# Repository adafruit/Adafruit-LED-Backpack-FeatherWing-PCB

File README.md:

## Adafruit LED Backpack FeatherWing PCB
&nbsp; <br />
Click to purchase from the Adafruit Shop:
- [Adafruit 4-Digit 7-Segment LED Matrix Display FeatherWing](https://www.adafruit.com/product/3088)
- [Adafruit 14-Segment Alphanumeric LED FeatherWing](https://www.adafruit.com/product/3089)

These are the Eagle CAD files for the Adafruit LED FeatherWings Backpack breakouts:

### 7-segment

This is the Adafruit 4-Digit 7-Segment LED Matrix Display FeatherWing! This 7-segment FeatherWing backpack makes it really easy to add a 4-digit numeric display with decimal points and even 'second colon dots' for making a clock.

This version does not come with an LED matrix. Its also available in combo packs of Blue, Green, Red, White, or Yellow which we recommend since you'll know you have a working LED matrix. Not guaranteed to work with any other 7-segment modules.

- http://www.adafruit.com/products/3088
- http://www.adafruit.com/products/3106
- http://www.adafruit.com/products/3107
- http://www.adafruit.com/products/3108
- http://www.adafruit.com/products/3109
- http://www.adafruit.com/products/3110

### 14-segment

This is the Adafruit 0.56" 4-Digit 14-Segment Display FeatherWing! This 14-segment FeatherWing backpack makes it really easy to add a bright alphanumeric display that shows letters and numbers in a beautiful hue. It's super bright and designed for viewing from distances up to 23 feet (7 meters) away.

14-Segment Matrices like these are 'multiplexed' - so to control all the fourteen-segment LEDs you need 18 pins. That's a lot of pins, and there are driver chips like the MAX7219 that can control a matrix for you but there's a lot of wiring to set up and they take up a ton of space. Wouldn't it be awesome if you could control a matrix without tons of wiring? That's where these Alphanumeric LED Matrix FeatherWings come in, they make it really easy to add a 4-digit alphanumeric display with decimal points.

- http://www.adafruit.com/products/3089
- http://www.adafruit.com/products/3127
- http://www.adafruit.com/products/3128
- http://www.adafruit.com/products/3129
- http://www.adafruit.com/products/3130
- http://www.adafruit.com/products/3131
- http://www.adafruit.com/products/3132

These displays use I2C to communicate, 2 pins are required to 
interface. There are multiple selectable I2C addresses. For backpacks 
with 3 Address Select pins: 0x70 thru 0x77

### License

Adafruit invests time and resources providing this open source design, please support Adafruit and open-source hardware by [purchasing products from Adafruit](https://www.adafruit.com)!

All text above must be included in any redistribution

Designed by Limor Fried/Ladyada for Adafruit Industries.
Creative Commons Attribution/Share-Alike, all text above must be included in any redistribution. 
See license.txt for additional information.

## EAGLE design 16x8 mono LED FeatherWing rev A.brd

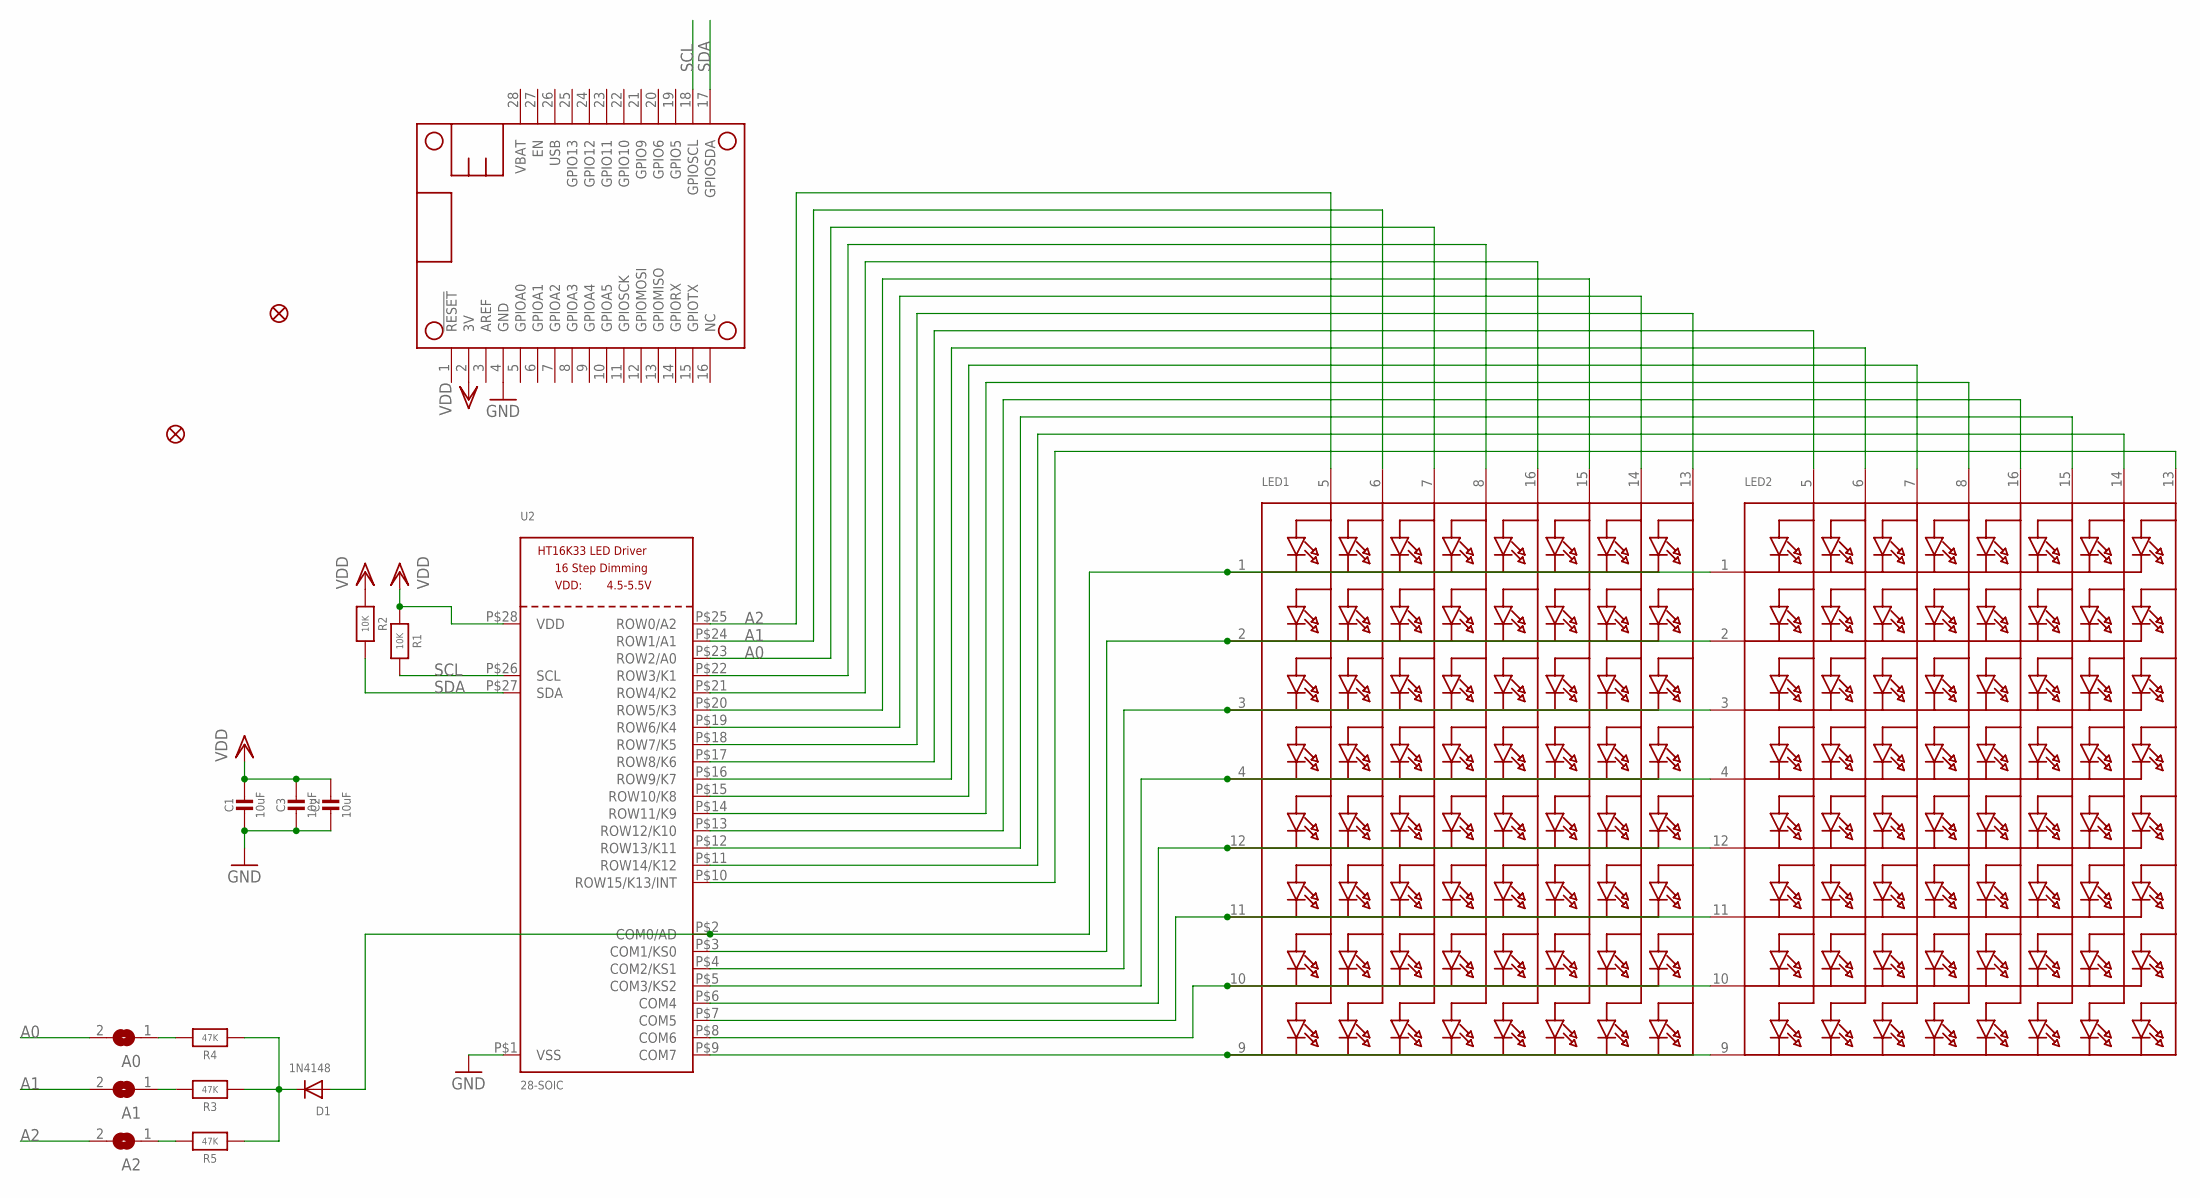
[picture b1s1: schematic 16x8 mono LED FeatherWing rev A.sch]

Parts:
A0, A1, A2: SOLDERJUMPERREFLOW_NOPASTE; SOLDERJUMPER_REFLOW_NOPASTE
C1, C2, C3: 10uF; 0805-NO
D1: 1N4148; SOD-323F
FID1, FID2: FIDUCIAL""; FIDUCIAL_1MM
LED1, LED2: DISP_SEGMENT_8X8_ROWCATHODE; SEGMENT_BL-M07C881UR
MS1: FEATHERWING
R1, R2: 10K; 0805-NO
R3, R4, R5: 47K; 0805-NO
U2: 28-SOIC; SOP28_300MIL_SKINNY

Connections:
A0: A0.2, LED1.7 (A3), U2.P$23 (ROW2/A0)
A1: A1.2, LED1.6 (A2), U2.P$24 (ROW1/A1)
A2: A2.2, LED1.5 (A1), U2.P$25 (ROW0/A2)
GND: C1.2, C2.2, C3.2, MS1.4 (GND), U2.P$1 (VSS)
unnamed: LED1.9 (K8), LED2.9 (K8), U2.P$9 (COM7)
unnamed: LED1.10 (K7), LED2.10 (K7), U2.P$8 (COM6)
unnamed: LED1.11 (K6), LED2.11 (K6), U2.P$7 (COM5)
unnamed: LED1.12 (K5), LED2.12 (K5), U2.P$6 (COM4)
unnamed: LED1.4 (K4), LED2.4 (K4), U2.P$5 (COM3/KS2)
unnamed: LED1.3 (K3), LED2.3 (K3), U2.P$4 (COM2/KS1)
unnamed: LED1.2 (K2), LED2.2 (K2), U2.P$3 (COM1/KS0)
unnamed: D1.A, LED1.1 (K1), LED2.1 (K1), U2.P$2 (COM0/AD)
unnamed: A2.1, R5.2
unnamed: LED2.14 (A7), U2.P$11 (ROW14/K12)
unnamed: LED2.15 (A6), U2.P$12 (ROW13/K11)
unnamed: LED2.13 (A8), U2.P$10 (ROW15/K13/INT)
unnamed: D1.C, R3.1, R4.1, R5.1
unnamed: A1.1, R3.2
unnamed: A0.1, R4.2
unnamed: LED1.13 (A8), U2.P$18 (ROW7/K5)
unnamed: LED1.14 (A7), U2.P$19 (ROW6/K4)
unnamed: LED1.16 (A5), U2.P$21 (ROW4/K2)
unnamed: LED1.8 (A4), U2.P$22 (ROW3/K1)
unnamed: LED1.15 (A6), U2.P$20 (ROW5/K3)
unnamed: LED2.5 (A1), U2.P$17 (ROW8/K6)
unnamed: LED2.6 (A2), U2.P$16 (ROW9/K7)
unnamed: LED2.8 (A4), U2.P$14 (ROW11/K9)
unnamed: LED2.7 (A3), U2.P$15 (ROW10/K8)
unnamed: LED2.16 (A5), U2.P$13 (ROW12/K10)
SCL: MS1.18 (GPIOSCL), R1.2, U2.P$26 (SCL)
SDA: MS1.17 (GPIOSDA), R2.2, U2.P$27 (SDA)
VDD: C1.1, C2.1, C3.1, MS1.2 (3V), R1.1, R2.1, U2.P$28 (VDD)

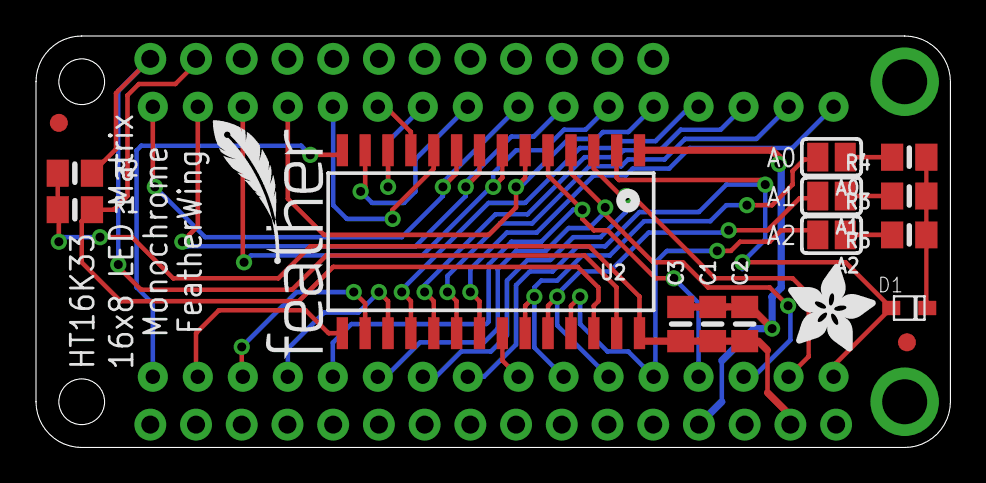
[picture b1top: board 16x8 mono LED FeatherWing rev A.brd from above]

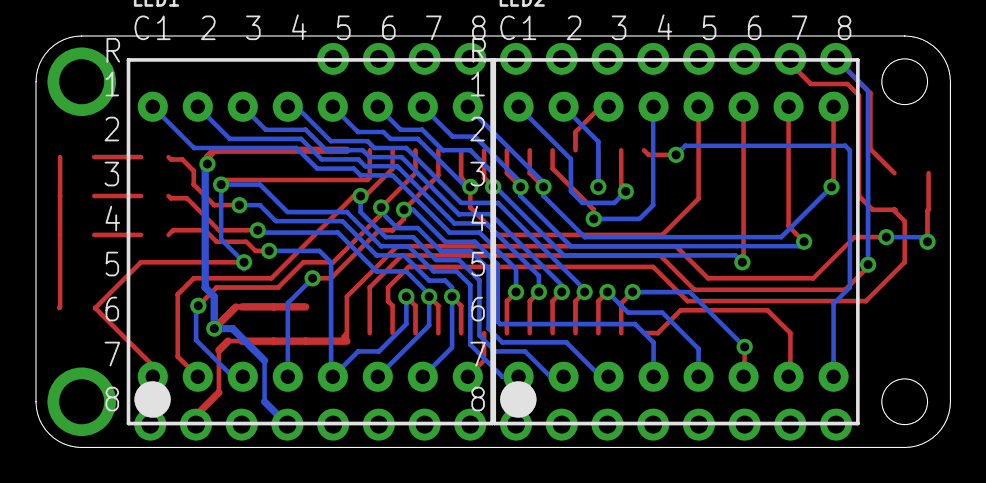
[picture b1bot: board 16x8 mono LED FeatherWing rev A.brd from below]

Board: 2 copper layers, 50.8 x 22.9 mm, 20 parts (3 on the bottom side), 32 nets.

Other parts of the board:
U$1: FEATHERLOGO_SMALL
U$2: ADAFRUIT_5MM

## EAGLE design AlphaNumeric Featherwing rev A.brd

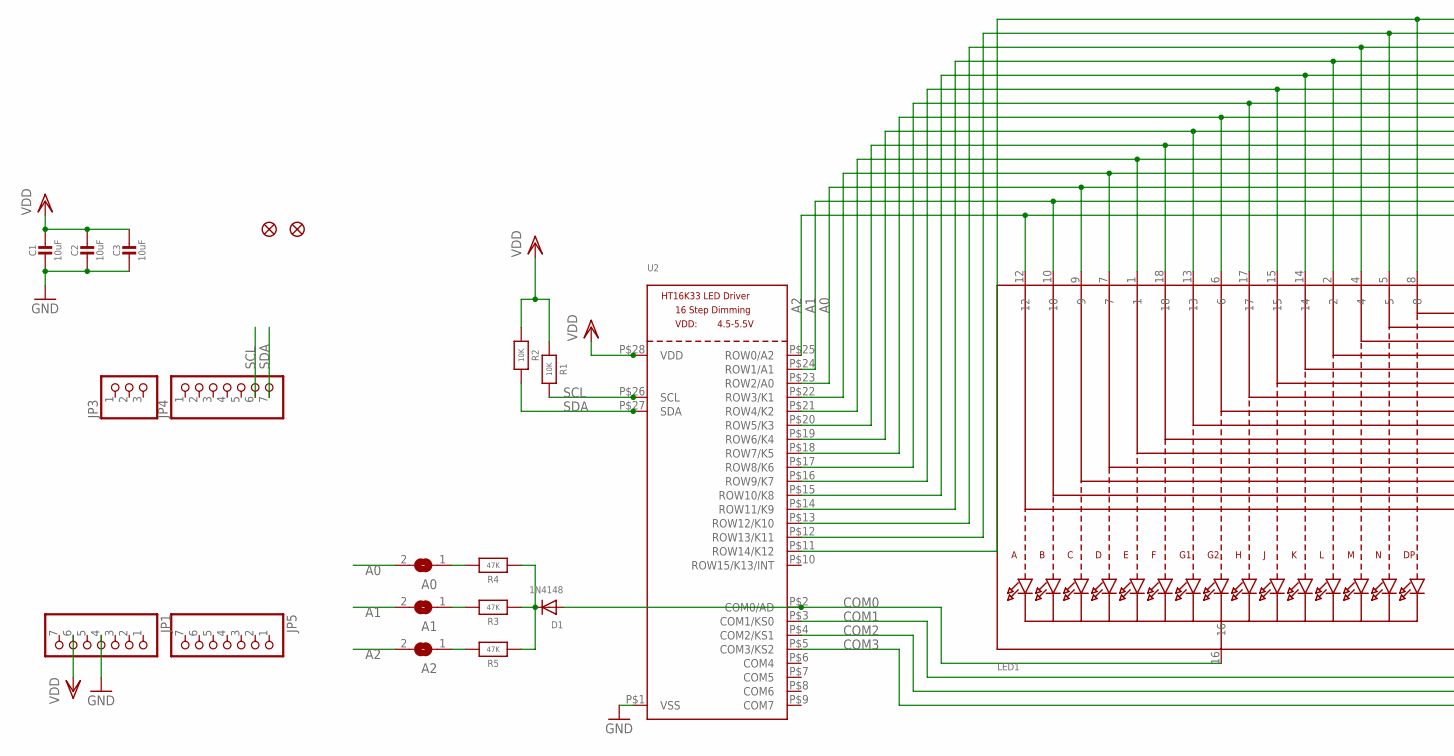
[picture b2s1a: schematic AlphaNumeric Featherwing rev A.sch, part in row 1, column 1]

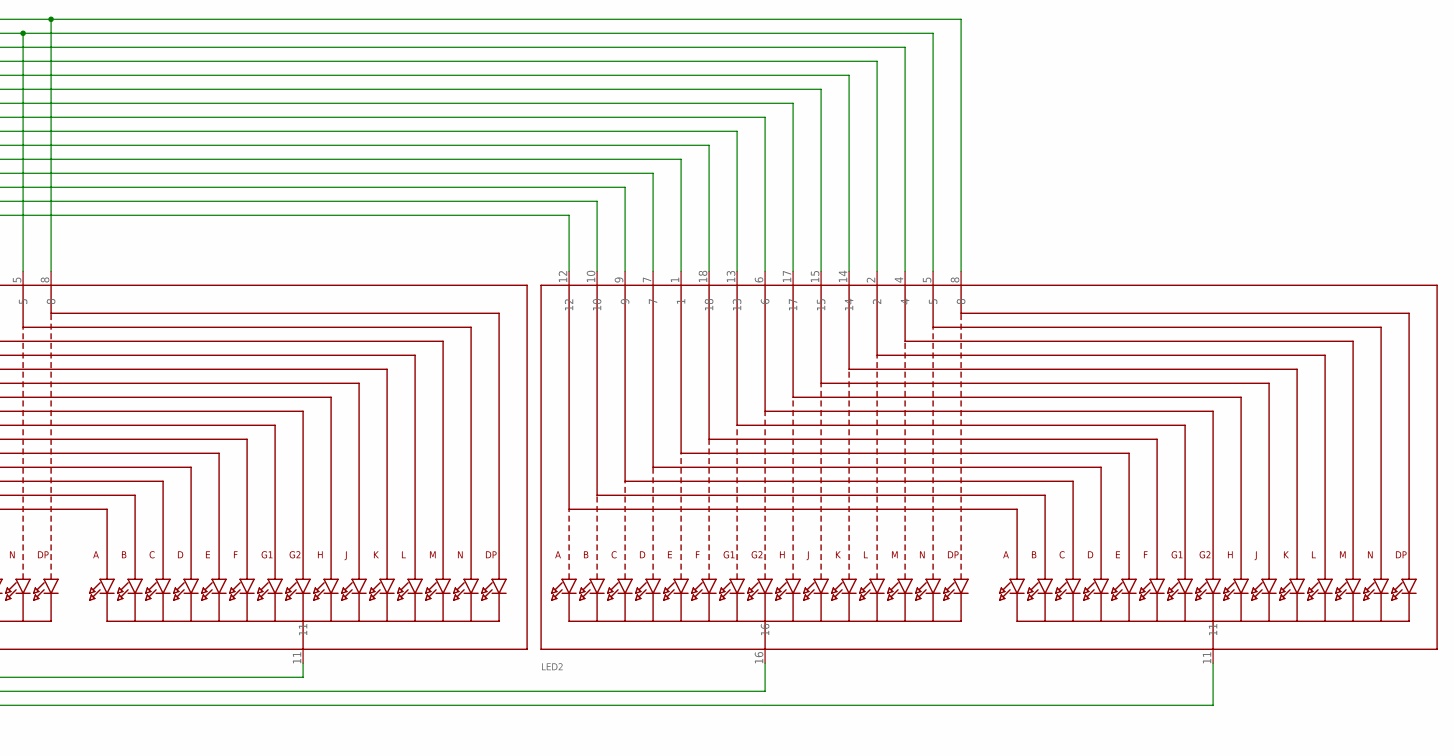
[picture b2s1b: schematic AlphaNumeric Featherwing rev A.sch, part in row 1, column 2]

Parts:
A0, A1, A2: SOLDERJUMPERREFLOW_NOPASTE; SOLDERJUMPER_REFLOW_NOPASTE
C1, C2, C3: 10uF; 0805-NO
D1: 1N4148; SOD-323F
JP1, JP4, JP5: HEADER-1X770MIL; 1X07_ROUND_70
JP3: HEADER-1X3ROUND; 1X03_ROUND
LED1, LED2: DISP_SEGMENT_STARBURST_DUAL_COMMONCATHODE; SEGMENT_STARTBUST_DUAL_KWA-541CBB
R1, R2: 10K; 0805-NO
R3, R4, R5: 47K; 0805-NO
U2: HT16K33_SOP28_SKINNY; SOP28_300MIL_SKINNY
U$1, U$2: FIDUCIAL""; FIDUCIAL_1MM

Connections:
A0: A0.2, LED1.9, LED2.9, U2.P$23 (ROW2/A0)
A1: A1.2, LED1.10, LED2.10, U2.P$24 (ROW1/A1)
A2: A2.2, LED1.12, LED2.12, U2.P$25 (ROW0/A2)
COM0: D1.A, LED1.16, U2.P$2 (COM0/AD)
COM1: LED1.11, U2.P$3 (COM1/KS0)
COM2: LED2.16, U2.P$4 (COM2/KS1)
COM3: LED2.11, U2.P$5 (COM3/KS2)
GND: C1.2, C2.2, C3.2, JP1.4, U2.P$1 (VSS)
unnamed: D1.C, R3.1, R4.1, R5.1
unnamed: LED1.17, LED2.17, U2.P$17 (ROW8/K6)
unnamed: LED1.15, LED2.15, U2.P$16 (ROW9/K7)
unnamed: LED1.14, LED2.14, U2.P$15 (ROW10/K8)
unnamed: A2.1, R5.2
unnamed: LED1.2, LED2.2, U2.P$14 (ROW11/K9)
unnamed: LED1.4, LED2.4, U2.P$13 (ROW12/K10)
unnamed: LED1.7, LED2.7, U2.P$22 (ROW3/K1)
unnamed: LED1.1, LED2.1, U2.P$21 (ROW4/K2)
unnamed: LED1.18, LED2.18, U2.P$20 (ROW5/K3)
unnamed: LED1.13, LED2.13, U2.P$19 (ROW6/K4)
unnamed: LED1.5, LED2.5, U2.P$12 (ROW13/K11)
unnamed: LED1.8, LED2.8, U2.P$11 (ROW14/K12)
unnamed: LED1.6, LED2.6, U2.P$18 (ROW7/K5)
unnamed: A1.1, R3.2
unnamed: A0.1, R4.2
SCL: JP4.6, R1.2, U2.P$26 (SCL)
SDA: JP4.7, R2.2, U2.P$27 (SDA)
VDD: C1.1, C2.1, C3.1, JP1.6, R1.1, R2.1, U2.P$28 (VDD)

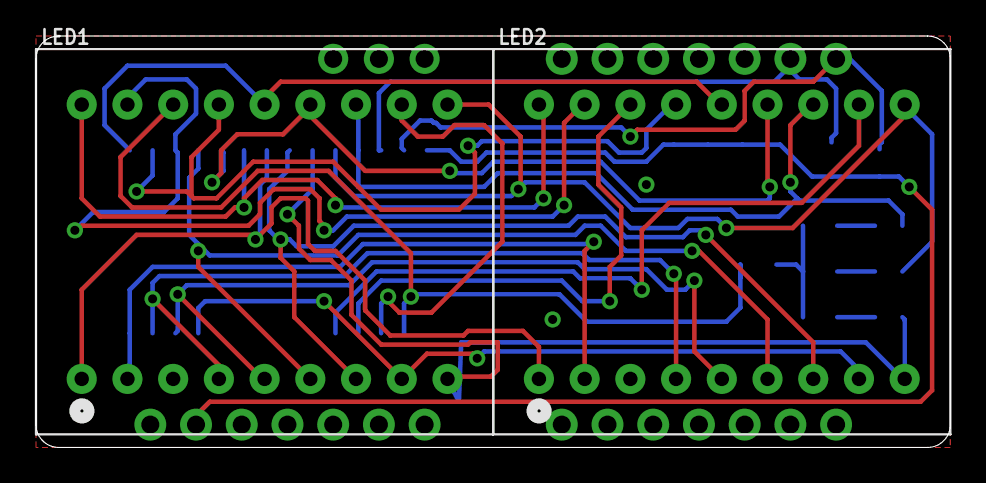
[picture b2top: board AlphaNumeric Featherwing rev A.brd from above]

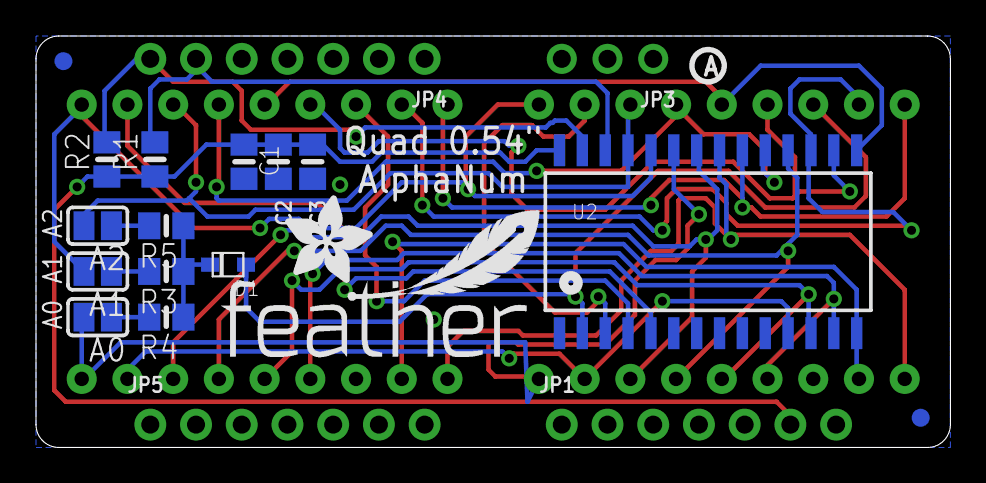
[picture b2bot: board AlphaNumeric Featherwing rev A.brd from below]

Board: 2 copper layers, 50.8 x 22.9 mm, 24 parts (22 on the bottom side), 27 nets.

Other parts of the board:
U$3: PCBFEAT-REV-040
U$4: FEATHERLOGO_MED
U$5: ADAFRUIT_5MM

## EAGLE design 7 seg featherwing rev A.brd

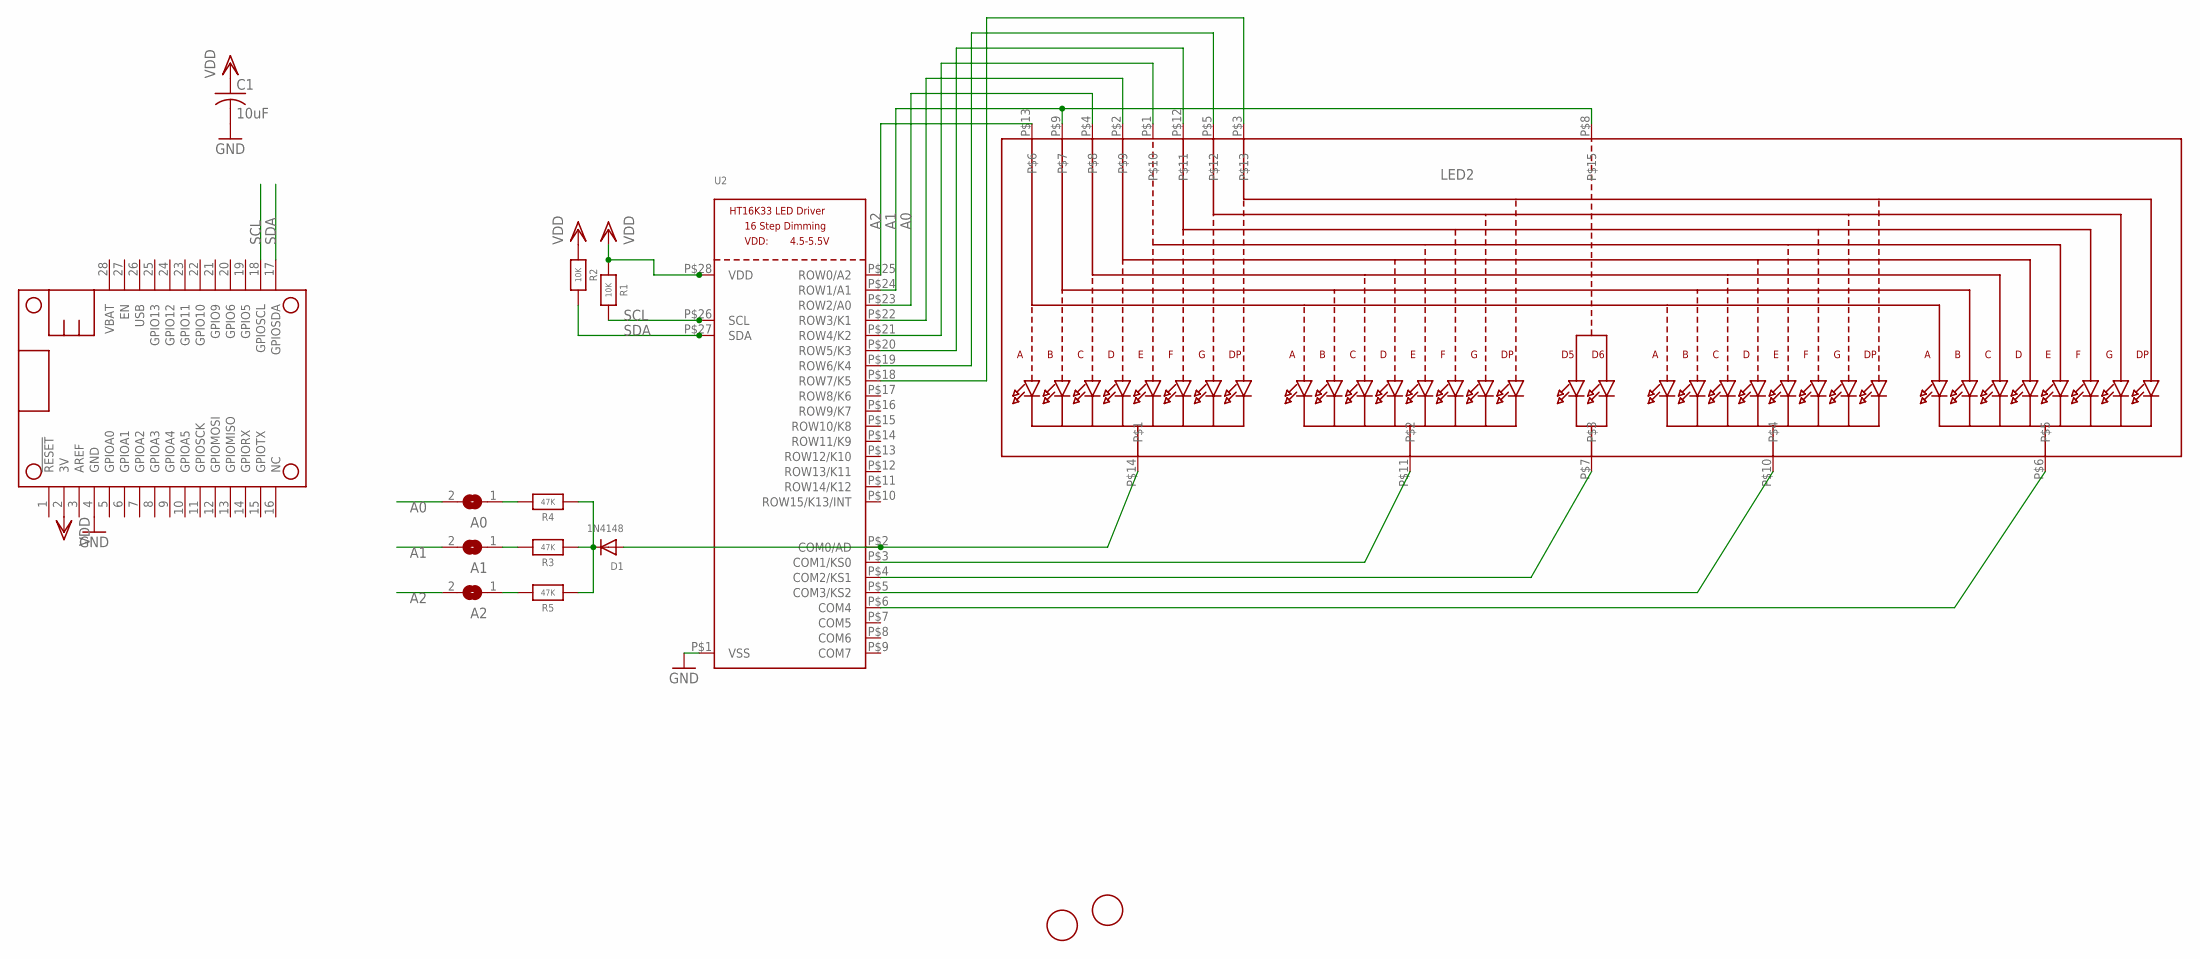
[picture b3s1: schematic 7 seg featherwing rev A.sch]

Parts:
A0, A1, A2: SOLDERJUMPERREFLOW_NOPASTE; SOLDERJUMPER_REFLOW_NOPASTE
C1: 10uF; C0805K
D1: 1N4148; SOD-323F
LED2: DISP_SEGMENT_4DIGIT_BL-Q56C43; SEGMENT-BL-Q56C43
MS1: FEATHERWING
R1, R2: 10K; 0805-NO
R3, R4, R5: 47K; 0805-NO
U2: HT16K33_SOP28_SKINNY; SOP28_300MIL_SKINNY
U$1, U$2: FIDUCIAL; FIDUCIAL_1MM

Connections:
A0: A0.2, LED2.P$4, U2.P$23 (ROW2/A0)
A1: A1.2, LED2.P$8, LED2.P$9, U2.P$24 (ROW1/A1)
A2: A2.2, LED2.P$13, U2.P$25 (ROW0/A2)
GND: C1.2, MS1.4 (GND), U2.P$1 (VSS)
unnamed: D1.C, R3.1, R4.1, R5.1
unnamed: D1.A, LED2.P$14, U2.P$2 (COM0/AD)
unnamed: LED2.P$11, U2.P$3 (COM1/KS0)
unnamed: LED2.P$7, U2.P$4 (COM2/KS1)
unnamed: LED2.P$10, U2.P$5 (COM3/KS2)
unnamed: LED2.P$6, U2.P$6 (COM4)
unnamed: A2.1, R5.2
unnamed: LED2.P$2, U2.P$22 (ROW3/K1)
unnamed: LED2.P$1, U2.P$21 (ROW4/K2)
unnamed: LED2.P$12, U2.P$20 (ROW5/K3)
unnamed: LED2.P$5, U2.P$19 (ROW6/K4)
unnamed: LED2.P$3, U2.P$18 (ROW7/K5)
unnamed: A1.1, R3.2
unnamed: A0.1, R4.2
SCL: MS1.18 (GPIOSCL), R1.2, U2.P$26 (SCL)
SDA: MS1.17 (GPIOSDA), R2.2, U2.P$27 (SDA)
VDD: C1.1, MS1.2 (3V), R1.1, R2.1, U2.P$28 (VDD)

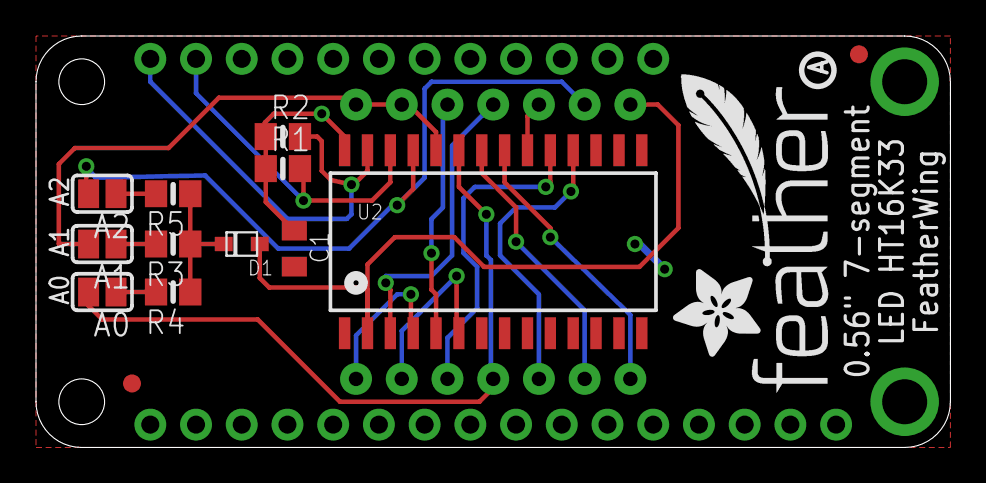
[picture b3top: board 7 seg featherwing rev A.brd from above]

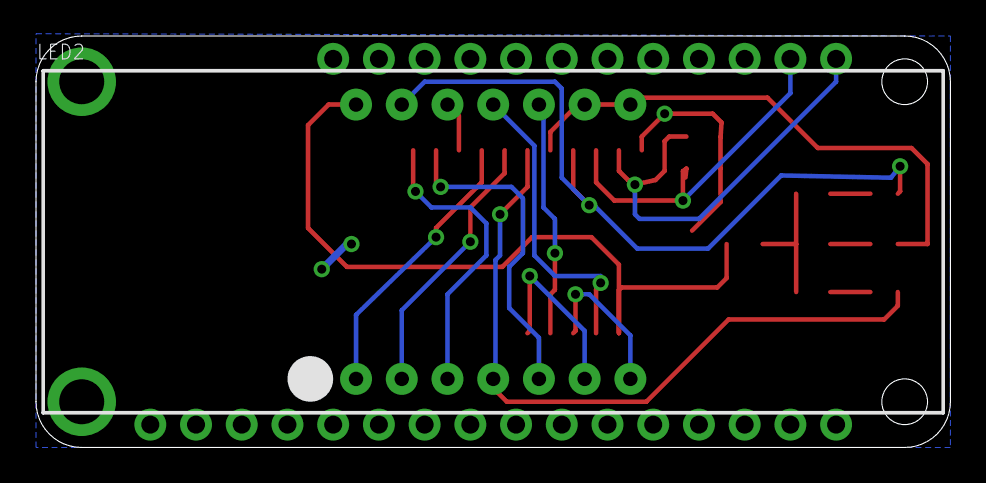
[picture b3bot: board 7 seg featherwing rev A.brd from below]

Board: 2 copper layers, 50.8 x 22.9 mm, 18 parts (2 on the bottom side), 21 nets.

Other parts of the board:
U$3: ADAFRUIT_5MM
U$4: PCBFEAT-REV-040
U$5: FEATHERLOGO_MED

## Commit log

2016-04-27 7-seg
2016-05-04 alphanum!
2016-05-20 16x8 mono
